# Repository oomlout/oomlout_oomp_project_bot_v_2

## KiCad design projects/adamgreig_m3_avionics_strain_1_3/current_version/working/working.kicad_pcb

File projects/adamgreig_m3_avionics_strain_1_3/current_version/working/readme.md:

# m3_avionics
 
## summary 
* id: adamgreig_m3_avionics_strain_1_3
* user: adamgreig
* name: m3_avionics
* board: strain_1_3
* repo: https://github.com/adamgreig/m3-avionics
* src_file_repo_kicad_pcb: m3dl/strain_1-3/strain_1-3.kicad_pcb
* src_file_repo_kicad_pcb_link: https://github.com/adamgreig/m3-avionics/tree/master/m3dl/strain_1-3/strain_1-3.kicad_pcb

* src_file_repo_sch: m3dl/strain_1-3/strain_1-3.sch
* src_file_repo_sch_link: https://github.com/adamgreig/m3-avionics/tree/master/m3dl/strain_1-3/strain_1-3.sch
* full details link: https://github.com/oomlout/oomlout_oomp_project_bot_v_2/tree/main/projects/adamgreig_m3_avionics_strain_1_3/current_version/working  

## schematic  
  
[schematic (pdf)](working_schematic.pdf) 

## pcb  

[board (pdf)](working.pdf)  

## working_bom
| Id | Designator | Footprint | Quantity | Designation | Supplier and ref |  | None | 
| --- | --- | --- | --- | --- | --- | --- | --- | 
| 1 | C1,C3,C4,C6,C15,C17 | 0603-L | 6 | 1n |  |  | [''] | 
| 2 | C2,C5,C16 | 0603-L | 3 | 10n |  |  | [''] | 
| 3 | C7,C8,C11,C12,C18,C20 | 0603-L | 6 | 8.2n |  |  | [''] | 
| 4 | C9,C10,C13,C14,C19,C21 | 0603-L | 6 | 82n |  |  | [''] | 
| 5 | IC1,IC3,IC6 | MSOP-8 | 3 | AD8226 |  |  | [''] | 
| 6 | IC2,IC4,IC7 | SC-70-5 | 3 | AD8541 |  |  | [''] | 
| 7 | IC5,IC8,IC9 | MSOP-8 | 3 | AD8656 |  |  | [''] | 
| 8 | J1 | TFML-110-02-L-D | 1 | WEST TOP |  |  | [''] | 
| 9 | J2 | TFML-110-02-L-D | 1 | EAST TOP |  |  | [''] | 
| 10 | J5 | TFML-110-02-L-D | 1 | SOUTH TOP |  |  | [''] | 
| 11 | R1,R2,R3,R4,R19,R20 | 0603-L | 6 | 3.74K |  |  | [''] | 
| 12 | R5,R6,R7,R8,R21,R22 | 0603-L | 6 | 10K |  |  | [''] | 
| 13 | R11,R12,R24 | 0603-L | 3 | 1.69K |  |  | [''] | 
| 14 | R13,R14,R25 | 0603-L | 3 | 6.04K |  |  | [''] | 
| 15 | R15,R16,R26 | 0603-L | 3 | 562R |  |  | [''] | 
| 16 | R17,R18,R27 | 0603-L | 3 | 17.8K |  |  | [''] | 
| 17 | J7 | Connector_Molex_PicoBlade_53048-0410 | 1 | S1 |  |  | [''] | 
| 18 | J8 | Connector_Molex_PicoBlade_53048-0410 | 1 | S3 |  |  | [''] | 
| 19 | J9 | Connector_Molex_PicoBlade_53048-0410 | 1 | S2 |  |  | [''] | 
| 20 | C35,C37 | 0402-L | 2 | 1u |  |  | [''] | 
| 21 | R32 | 0402-L | 1 | 110k |  |  | [''] | 
| 22 | IC10 | DFN-6-EP-ONSEMI | 1 | NCP380 |  |  | [''] | 
| 23 | J3 | SFML-110-02-L-D-LC | 1 | WEST BOT |  |  | [''] | 
| 24 | J4 | SFML-110-02-L-D-LC | 1 | EAST BOT |  |  | [''] | 
| 25 | J6 | SFML-110-02-L-D-LC | 1 | SOUTH BOT |  |  | [''] | 
| 26 | R9,R10,R23 | 0603-L | 3 | 330 |  |  | [''] | 
| 27 | C22,C23,C24,C25,C26,C27,C28,C29,C30,C31,C32,C33 | 0603-L | 12 | 100n |  |  | [''] | 
| 28 | C34 | 0603-L | 1 | 10u |  |  | [''] | 
| 29 | R28,R29,R30 | 0603 | 3 | 0R |  |  | [''] | 
| 30 | D1,D2,D3,D4,D5,D6,D7,D8,D9 | 0402 | 9 | ESD_DIODE |  |  | [''] | 

## bom_schematic
| Ref | Qnty | Value | Cmp name | Footprint | Description | Vendor | DNP | 
| --- | --- | --- | --- | --- | --- | --- | --- | 
| C1, C3, C4, C6, C15, C17 | 6 | 1n | C_Small | Capacitors_SMD:C_0603 |  |  |  | 
| C2, C5, C16 | 3 | 10n | C_Small | Capacitors_SMD:C_0603 |  |  |  | 
| C7, C8, C11, C12, C18, C20 | 6 | 8.2n | C_Small | Capacitors_SMD:C_0603 |  |  |  | 
| C9, C10, C13, C14, C19, C21 | 6 | 82n | C_Small | Capacitors_SMD:C_0603 |  |  |  | 
| C22, C23, C24, C25, C26, C27, C28, C29, C30, C31, C32, C33 | 12 | 100n | C_Small | agg:0603-L |  |  |  | 
| C34 | 1 | 10u | C_Small | agg:0603-L |  |  |  | 
| C35, C37 | 2 | 1u | C_Small | agg:0402-L |  |  |  | 
| D1, D2, D3, D4, D5, D6, D7, D8, D9 | 9 | ESD_DIODE | ESD_DIODE | agg:0402 |  |  |  | 
| IC1, IC3, IC6 | 3 | AD8226 | AD8226 | agg:MSOP-8 |  |  |  | 
| IC2, IC4, IC7 | 3 | AD8541 | AD8541 | agg:SC-70-5 |  |  |  | 
| IC5, IC8, IC9 | 3 | AD8656 | AD8656 | agg:MSOP-8 |  |  |  | 
| IC10 | 1 | NCP380 | NCP380 | agg:DFN-6-EP-ONSEMI |  |  |  | 
| J1 | 1 | WEST TOP | CONN_02x10 | agg:TFML-110-02-L-D |  |  |  | 
| J2 | 1 | EAST TOP | CONN_02x10 | agg:TFML-110-02-L-D |  |  |  | 
| J3 | 1 | WEST BOT | CONN_02x10 | agg:SFML-110-02-L-D-LC |  |  |  | 
| J4 | 1 | EAST BOT | CONN_02x10 | agg:SFML-110-02-L-D-LC |  |  |  | 
| J5 | 1 | SOUTH TOP | CONN_02x10 | agg:TFML-110-02-L-D |  |  |  | 
| J6 | 1 | SOUTH BOT | CONN_02x10 | agg:SFML-110-02-L-D-LC |  |  |  | 
| J7 | 1 | S1 | CONN_01x04 | Connectors_Molex:Connector_Molex_PicoBlade_53048-0410 |  |  |  | 
| J8 | 1 | S3 | CONN_01x04 | Connectors_Molex:Connector_Molex_PicoBlade_53048-0410 |  |  |  | 
| J9 | 1 | S2 | CONN_01x04 | Connectors_Molex:Connector_Molex_PicoBlade_53048-0410 |  |  |  | 
| R1, R2, R3, R4, R19, R20 | 6 | 3.74K | R | Resistors_SMD:R_0603 |  |  |  | 
| R5, R6, R7, R8, R21, R22 | 6 | 10K | R | Resistors_SMD:R_0603 |  |  |  | 
| R9, R10, R23 | 3 | 330 | R | Resistors_SMD:R_0603 |  |  |  | 
| R11, R12, R24 | 3 | 1.69K | R | Resistors_SMD:R_0603 |  |  |  | 
| R13, R14, R25 | 3 | 6.04K | R | Resistors_SMD:R_0603 |  |  |  | 
| R15, R16, R26 | 3 | 562R | R | Resistors_SMD:R_0603 |  |  |  | 
| R17, R18, R27 | 3 | 17.8K | R | Resistors_SMD:R_0603 |  |  |  | 
| R28, R29, R30 | 3 | 0R | R | agg:0603 |  |  |  | 
| R32 | 1 | 110k | R | agg:0402-L |  |  |  |

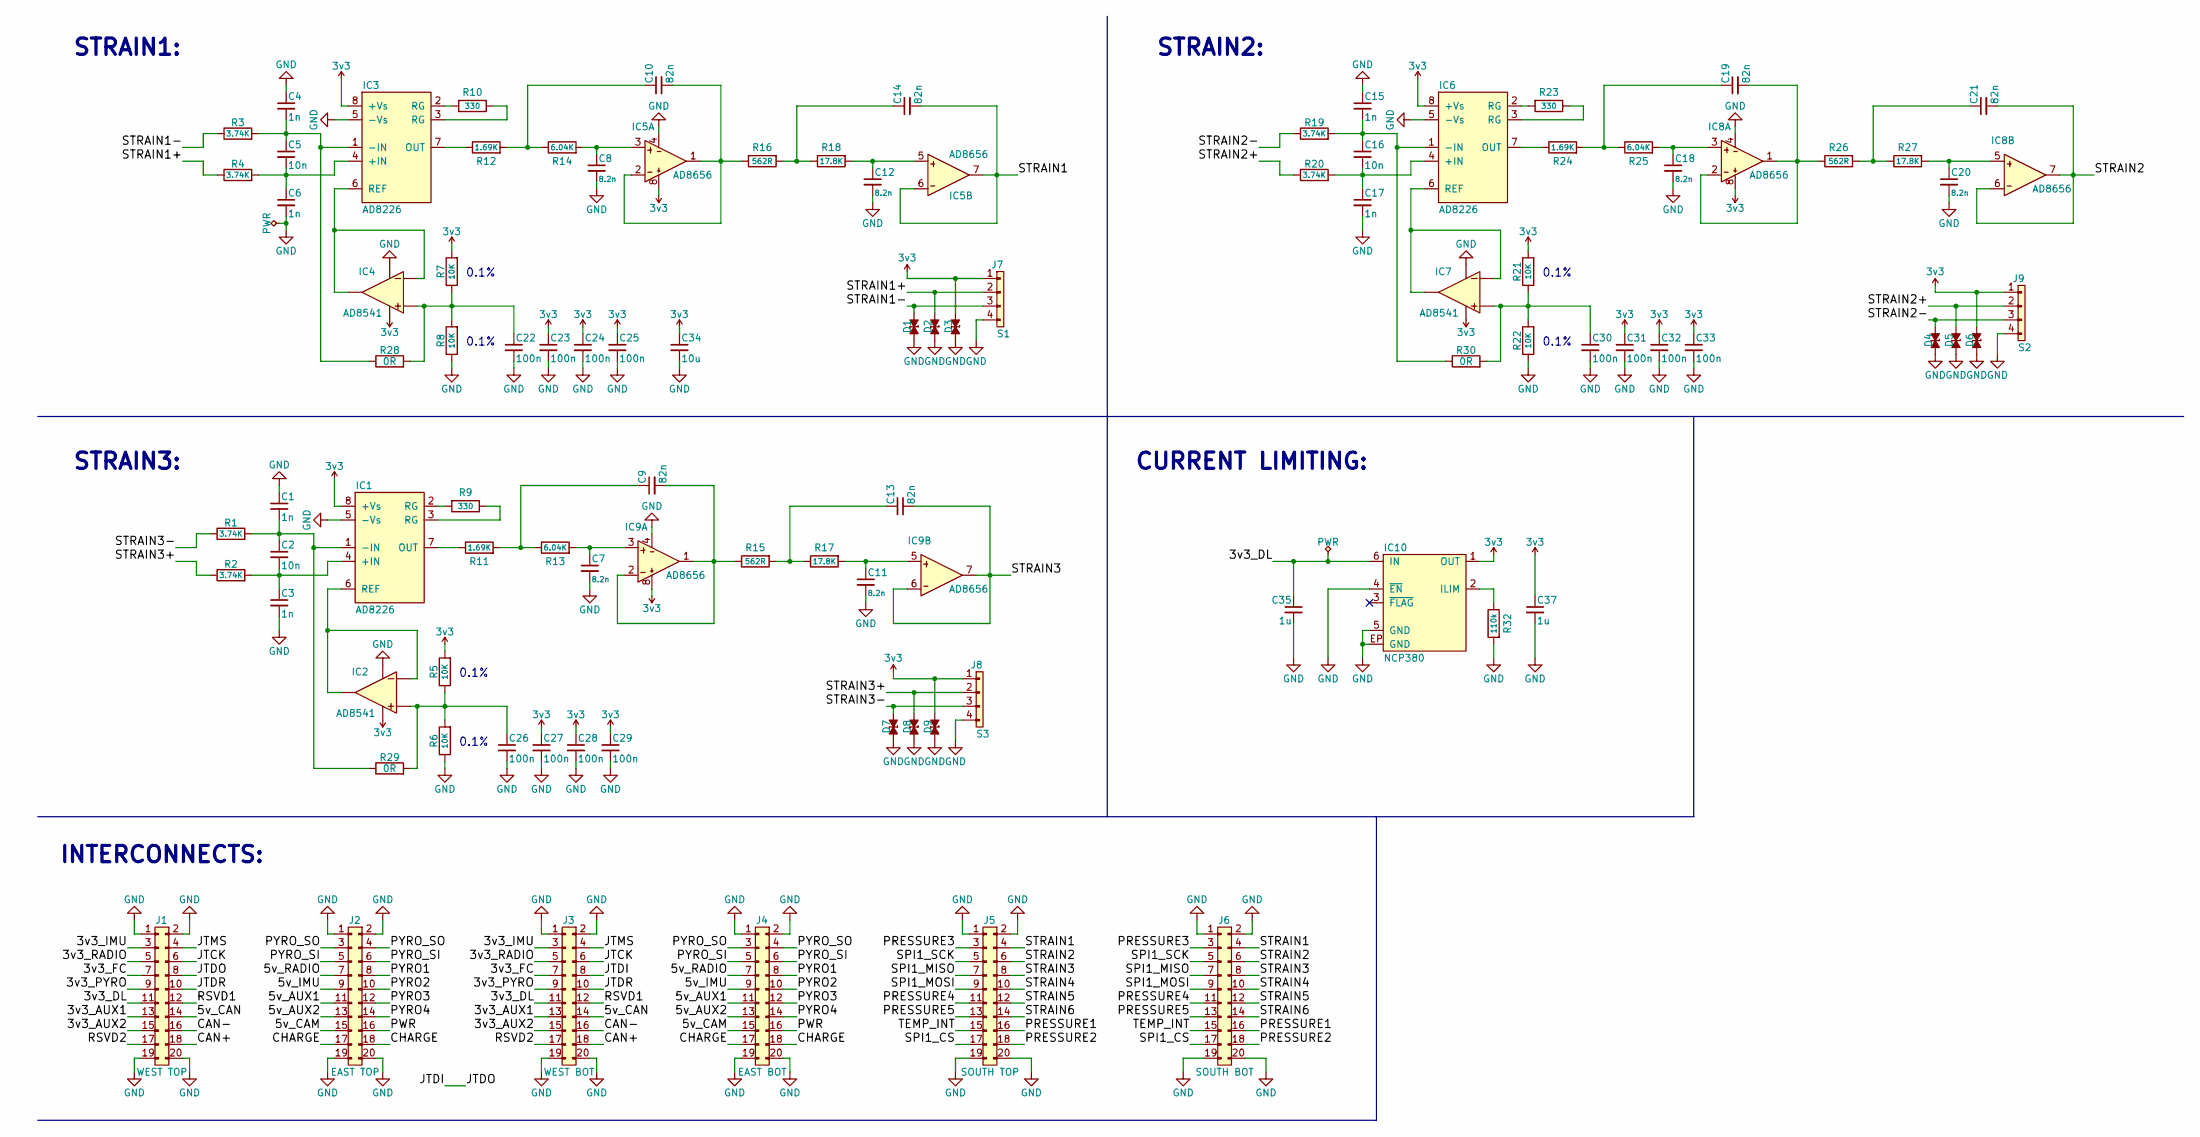
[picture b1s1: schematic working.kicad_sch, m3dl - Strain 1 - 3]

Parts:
C1, C3, C4, C6, C15, C17: 1n; C_0603; Farnell 1813443
C2, C5, C16: 10n; C_0603; Farnell 1457729
C7, C8, C11, C12, C18, C20: 8.2n; C_0603; Farnell 1865464
C9, C10, C13, C14, C19, C21: 82n; C_0603; Farnell 1865539
C22, C23, C24, C25, C26, C27, C28, C29, C30, C31, C32, C33: 100n; 0603-L; Farnell 2496834
C34: 10u; 0603-L; Farnell 2211164
C35, C37: 1u; 0402-L; Farnell 2346884
D1, D2, D3, D4, D5, D6, D7, D8, D9: ESD_DIODE; 0402; Farnell 2368169
IC1, IC3, IC6: AD8226; MSOP-8; Farnell 2462026
IC2, IC4, IC7: AD8541; SC-70-5; Farnell 1333254
IC5, IC8, IC9: AD8656; MSOP-8; Farnell 1858055
IC10: NCP380; DFN-6-EP-ONSEMI; Farnell 2464412
J1: WEST TOP; TFML-110-02-L-D
J2: EAST TOP; TFML-110-02-L-D
J3: WEST BOT; SFML-110-02-L-D-LC
J4: EAST BOT; SFML-110-02-L-D-LC
J5: SOUTH TOP; TFML-110-02-L-D
J6: SOUTH BOT; SFML-110-02-L-D-LC
J7: S1; Connector_Molex_PicoBlade_53048-0410
J8: S3; Connector_Molex_PicoBlade_53048-0410
J9: S2; Connector_Molex_PicoBlade_53048-0410
R1, R2, R3, R4, R19, R20: 3.74K; R_0603; Farnell 2059366
R5, R6, R7, R8, R21, R22: 10K; R_0603; Farnell 1697388
R9, R10, R23: 330; R_0603; Farnell 2502447
R11, R12, R24: 1.69K; R_0603; Farnell 2059339
R13, R14, R25: 6.04K; R_0603; Farnell 2059386
R15, R16, R26: 562R; R_0603; Farnell 1170763
R17, R18, R27: 17.8K; R_0603; Farnell 1170912
R28, R29, R30: 0R; 0603; Farnell 9331662
R32: 110k; 0402-L; Farnell 2502502

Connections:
3v3: C23.1, C24.1, C25.1, C27.1, C28.1, C29.1, C31.1, C32.1, C33.1, C34.1, C37.1, D3.2, D6.2, D9.2, IC1.8 (+Vs), IC2.5 (V+), IC3.8 (+Vs), IC4.5 (V+), IC5.8 (V+), IC6.8 (+Vs), IC7.5 (V+), IC8.8 (V+), IC9.8 (V+), IC10.1 (OUT), J7.1, J8.1, J9.1, R5.2, R7.2, R21.2
/3v3_AUX1: J1.13, J3.13
/3v3_AUX2: J1.15, J3.15
/3v3_DL: C35.1, IC10.6 (IN), J1.11, J3.11
/3v3_FC: J1.7, J3.7
/3v3_IMU: J1.3, J3.3
/3v3_PYRO: J1.9, J3.9
/3v3_RADIO: J1.5, J3.5
/5v_AUX1: J2.11, J4.11
/5v_AUX2: J2.13, J4.13
/5v_CAM: J2.15, J4.15
/5v_CAN: J1.14, J3.14
/5v_IMU: J2.9, J4.9
/5v_RADIO: J2.7, J4.7
/CAN+: J1.18, J3.18
/CAN-: J1.16, J3.16
/CHARGE: J2.17, J2.18, J4.17, J4.18
/JTCK: J1.6, J3.6
/JTDI: J1.8, J3.8
/JTDR: J1.10, J3.10
/JTMS: J1.4, J3.4
/PRESSURE1: J5.16, J6.16
/PRESSURE2: J5.18, J6.18
/PRESSURE3: J5.3, J6.3
/PRESSURE4: J5.11, J6.11
/PRESSURE5: J5.13, J6.13
/PWR: J2.16, J4.16
/PYRO1: J2.8, J4.8
/PYRO2: J2.10, J4.10
/PYRO3: J2.12, J4.12
/PYRO4: J2.14, J4.14
/PYRO_SI: J2.5, J2.6, J4.5, J4.6
/PYRO_SO: J2.3, J2.4, J4.3, J4.4
/RSVD1: J1.12, J3.12
/RSVD2: J1.17, J3.17
/SPI1_CS: J5.17, J6.17
/SPI1_MISO: J5.7, J6.7
/SPI1_MOSI: J5.9, J6.9
/SPI1_SCK: J5.5, J6.5
/STRAIN1: C14.2, IC5.6 (-IN), IC5.7 (OUT), J5.4, J6.4
/STRAIN1+: D2.2, J7.2, R4.1
/STRAIN1-: D1.2, J7.3, R3.1
/STRAIN2: C21.2, IC8.6 (-IN), IC8.7 (OUT), J5.6, J6.6
/STRAIN2+: D5.2, J9.2, R20.1
/STRAIN2-: D4.2, J9.3, R19.1
/STRAIN3: C13.2, IC9.6 (-IN), IC9.7 (OUT), J5.8, J6.8
/STRAIN3+: D8.2, J8.2, R2.1
/STRAIN3-: D7.2, J8.3, R1.1
/STRAIN4: J5.10, J6.10
/STRAIN5: J5.12, J6.12
/STRAIN6: J5.14, J6.14
/TEMP_INT: J5.15, J6.15
GND: C1.1, C3.2, C4.1, C6.2, C7.2, C8.2, C11.2, C12.2, C15.1, C17.2, C18.2, C20.2, C22.2, C23.2, C24.2, C25.2, C26.2, C27.2, C28.2, C29.2, C30.2, C31.2, C32.2, C33.2, C34.2, C35.2, C37.2, D1.1, D2.1, D3.1, D4.1, D5.1, D6.1, D7.1, D8.1, D9.1, IC1.5 (-Vs), IC2.2 (V-), IC3.5 (-Vs), IC4.2 (V-), IC5.4 (V-), IC6.5 (-Vs), IC7.2 (V-), IC8.4 (V-), IC9.4 (V-), IC10.4 (~EN), IC10.5 (GND), IC10.EP (GND), J1.1, J1.2, J1.19, J1.20, J2.1, J2.2, J2.19, J2.20, J3.1, J3.2, J3.19, J3.20, J4.1, J4.2, J4.19, J4.20, J5.1, J5.2, J5.19, J5.20, J6.1, J6.2, J6.19, J6.20, J7.4, J8.4, J9.4, R6.1, R8.1, R22.1, R32.2
unnamed: C1.2, C2.1, IC1.1 (-IN), R1.2, R29.1
unnamed: C2.2, C3.1, IC1.4 (+IN), R2.2
unnamed: C4.2, C5.1, IC3.1 (-IN), R3.2, R28.1
unnamed: C5.2, C6.1, IC3.4 (+IN), R4.2
unnamed: C7.1, IC9.3 (+IN), R13.2
unnamed: C8.1, IC5.3 (+IN), R14.2
unnamed: C9.1, R11.2, R13.1
unnamed: C9.2, IC9.1 (OUT), IC9.2 (-IN), R15.1
unnamed: C10.1, R12.2, R14.1
unnamed: C10.2, IC5.1 (OUT), IC5.2 (-IN), R16.1
unnamed: C11.1, IC9.5 (+IN), R17.2
unnamed: C12.1, IC5.5 (+IN), R18.2
unnamed: C13.1, R15.2, R17.1
unnamed: C14.1, R16.2, R18.1
unnamed: C15.2, C16.1, IC6.1 (-IN), R19.2, R30.1
unnamed: C16.2, C17.1, IC6.4 (+IN), R20.2
unnamed: C18.1, IC8.3 (+IN), R25.2
unnamed: C19.1, R24.2, R25.1
unnamed: C19.2, IC8.1 (OUT), IC8.2 (-IN), R26.1
unnamed: C20.1, IC8.5 (+IN), R27.2
unnamed: C21.1, R26.2, R27.1
unnamed: C22.1, IC4.3 (+), R7.1, R8.2, R28.2
unnamed: C26.1, IC2.3 (+), R5.1, R6.2, R29.2
unnamed: C30.1, IC7.3 (+), R21.1, R22.2, R30.2
unnamed: IC1.2 (RG), R9.2
unnamed: IC1.3 (RG), R9.1
unnamed: IC1.6 (REF), IC2.1 (OUT), IC2.4 (-)
unnamed: IC1.7 (OUT), R11.1
unnamed: IC3.2 (RG), R10.2
unnamed: IC3.3 (RG), R10.1
unnamed: IC3.6 (REF), IC4.1 (OUT), IC4.4 (-)
unnamed: IC3.7 (OUT), R12.1
unnamed: IC6.2 (RG), R23.2
unnamed: IC6.3 (RG), R23.1
unnamed: IC6.6 (REF), IC7.1 (OUT), IC7.4 (-)
unnamed: IC6.7 (OUT), R24.1
unnamed: IC10.2 (ILIM), R32.1

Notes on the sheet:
0.1%
INTERCONNECTS:
CURRENT LIMITING:
STRAIN3:
STRAIN2:
STRAIN1:

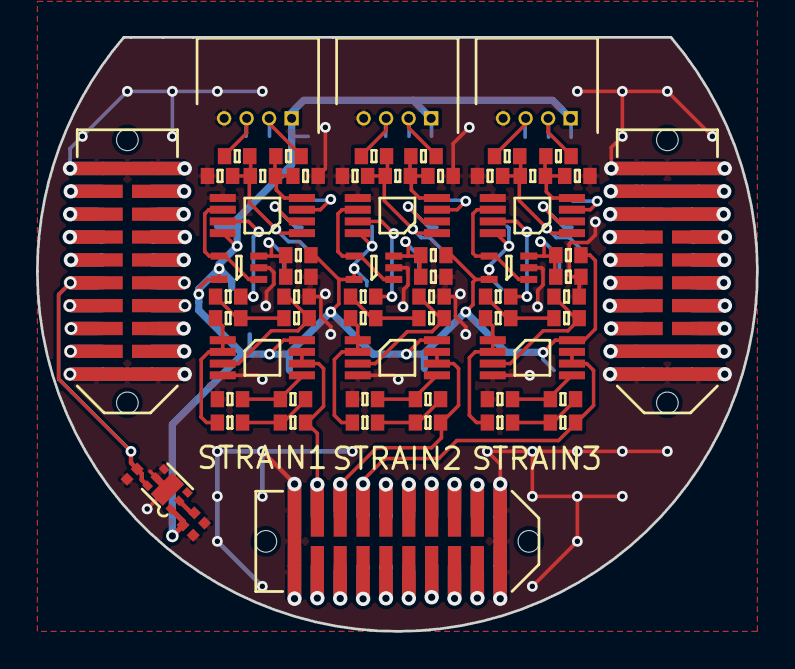
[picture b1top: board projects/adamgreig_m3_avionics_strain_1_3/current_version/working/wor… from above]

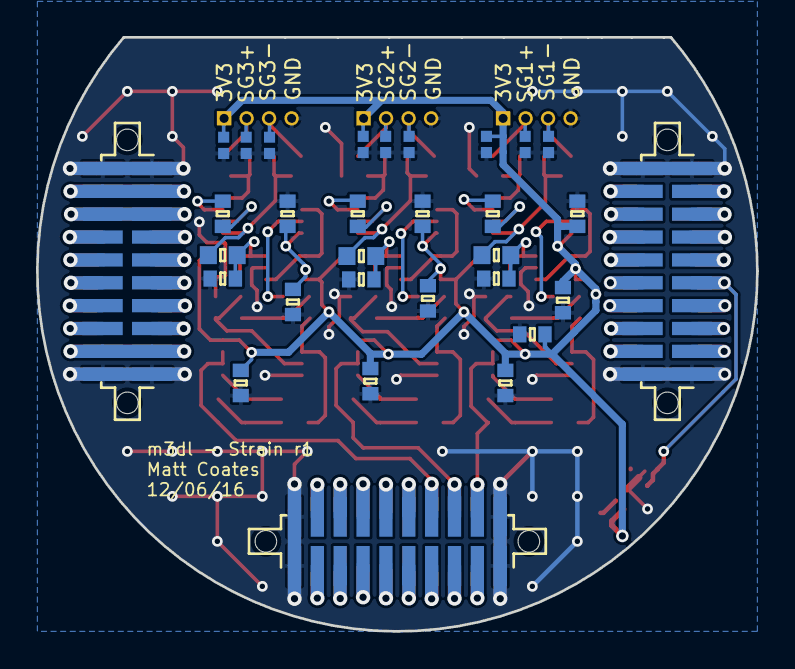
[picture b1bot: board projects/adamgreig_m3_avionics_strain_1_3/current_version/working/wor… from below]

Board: 2 copper layers, 40.0 x 33.0 mm, 95 parts (31 on the bottom side), 90 nets.

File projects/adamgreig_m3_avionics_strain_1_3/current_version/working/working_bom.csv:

"Id";"Designator";"Footprint";"Quantity";"Designation";"Supplier and ref";
1;"C1,C3,C4,C6,C15,C17";"0603-L";6;"1n";;;
2;"C2,C5,C16";"0603-L";3;"10n";;;
3;"C7,C8,C11,C12,C18,C20";"0603-L";6;"8.2n";;;
4;"C9,C10,C13,C14,C19,C21";"0603-L";6;"82n";;;
5;"IC1,IC3,IC6";"MSOP-8";3;"AD8226";;;
6;"IC2,IC4,IC7";"SC-70-5";3;"AD8541";;;
7;"IC5,IC8,IC9";"MSOP-8";3;"AD8656";;;
8;"J1";"TFML-110-02-L-D";1;"WEST TOP";;;
9;"J2";"TFML-110-02-L-D";1;"EAST TOP";;;
10;"J5";"TFML-110-02-L-D";1;"SOUTH TOP";;;
11;"R1,R2,R3,R4,R19,R20";"0603-L";6;"3.74K";;;
12;"R5,R6,R7,R8,R21,R22";"0603-L";6;"10K";;;
13;"R11,R12,R24";"0603-L";3;"1.69K";;;
14;"R13,R14,R25";"0603-L";3;"6.04K";;;
15;"R15,R16,R26";"0603-L";3;"562R";;;
16;"R17,R18,R27";"0603-L";3;"17.8K";;;
17;"J7";"Connector_Molex_PicoBlade_53048-0410";1;"S1";;;
18;"J8";"Connector_Molex_PicoBlade_53048-0410";1;"S3";;;
19;"J9";"Connector_Molex_PicoBlade_53048-0410";1;"S2";;;
20;"C35,C37";"0402-L";2;"1u";;;
21;"R32";"0402-L";1;"110k";;;
22;"IC10";"DFN-6-EP-ONSEMI";1;"NCP380";;;
23;"J3";"SFML-110-02-L-D-LC";1;"WEST BOT";;;
24;"J4";"SFML-110-02-L-D-LC";1;"EAST BOT";;;
25;"J6";"SFML-110-02-L-D-LC";1;"SOUTH BOT";;;
26;"R9,R10,R23";"0603-L";3;"330";;;
27;"C22,C23,C24,C25,C26,C27,C28,C29,C30,C31,C32,C33";"0603-L";12;"100n";;;
28;"C34";"0603-L";1;"10u";;;
29;"R28,R29,R30";"0603";3;"0R";;;
30;"D1,D2,D3,D4,D5,D6,D7,D8,D9";"0402";9;"ESD_DIODE";;;

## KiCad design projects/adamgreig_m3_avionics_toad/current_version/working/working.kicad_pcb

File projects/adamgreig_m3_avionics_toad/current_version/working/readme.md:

# m3_avionics
 
## summary 
* id: adamgreig_m3_avionics_toad
* user: adamgreig
* name: m3_avionics
* board: toad
* repo: https://github.com/adamgreig/m3-avionics
* src_file_repo_kicad_pcb: TOAD/pcb/TOAD.kicad_pcb
* src_file_repo_kicad_pcb_link: https://github.com/adamgreig/m3-avionics/tree/master/TOAD/pcb/TOAD.kicad_pcb

* src_file_repo_sch: TOAD/pcb/TOAD.sch
* src_file_repo_sch_link: https://github.com/adamgreig/m3-avionics/tree/master/TOAD/pcb/TOAD.sch
* full details link: https://github.com/oomlout/oomlout_oomp_project_bot_v_2/tree/main/projects/adamgreig_m3_avionics_toad/current_version/working  

## schematic  
  
[schematic (pdf)](working_schematic.pdf) 

## pcb  

[board (pdf)](working.pdf)  

## working_bom
| Id | Designator | Footprint | Quantity | Designation | Supplier and ref |  | None | 
| --- | --- | --- | --- | --- | --- | --- | --- | 
| 1 | C1,C33 | 0603-L | 2 | 2.2uF |  |  | [''] | 
| 2 | C2,C34 | 0402 | 2 | 100nF |  |  | [''] | 
| 3 | C3,C35 | 0402 | 2 | 220pF |  |  | [''] | 
| 4 | C4,C7,C8,C9,C12,C13,C14,C60 | 0402 | 8 | 100n |  |  | [''] | 
| 5 | C5,C37 | 0603-L | 2 | 1uF |  |  | [''] | 
| 6 | C6,C38 | 0402 | 2 | 100pF |  |  | [''] | 
| 7 | C10,C11 | 0603-L | 2 | 2u2 |  |  | [''] | 
| 8 | C15 | 0603 | 1 | 4u7 |  |  | [''] | 
| 9 | C16,C26,C31,C42,C43,C47 | 0603-L | 6 | 1u |  |  | [''] | 
| 10 | C17,C48 | 0402 | 2 | 3pF |  |  | [''] | 
| 11 | C18,C49 | 0402 | 2 | 33pF |  |  | [''] | 
| 12 | C19,C50 | 0402 | 2 | 3.9pF |  |  | [''] | 
| 13 | C20,C51 | 0402 | 2 | 1pF |  |  | [''] | 
| 14 | C21,C32,C36,C44,C58 | 0603-L | 5 | 100n |  |  | [''] | 
| 15 | C22,C52 | 0402 | 2 | 5.1pF |  |  | [''] | 
| 16 | C23,C53 | 0402 | 2 | 2.7pF |  |  | [''] | 
| 17 | C28,C30,C57,C59 | 0402 | 4 | 4.7pF |  |  | [''] | 
| 18 | C29,C46 | 0603-L | 2 | 10n |  |  | [''] | 
| 19 | C39,C45 | 0603-L | 2 | 4u7 |  |  | [''] | 
| 20 | C40,C41 | 0603-L | 2 | 1n |  |  | [''] | 
| 21 | D1,D2,D3,D4,D5,D6,D7,D15,D17,D18 | 0402-L | 10 | ESD_DIODE |  |  | [''] | 
| 22 | D8,D9,D10,D11,D12,D13,D14,D16 | 0603-LED | 8 | LED |  |  | [''] | 
| 23 | IC1 | LQFP-64 | 1 | STM32F405RxTx |  |  | [''] | 
| 24 | IC2,IC9 | QFN-20-EP-SI | 2 | Si4463 |  |  | [''] | 
| 25 | IC3 | MAX-M8Q | 1 | MAX-M8Q |  |  | [''] | 
| 26 | IC4 | SC-70-6 | 1 | SN74LVC1G0832 |  |  | [''] | 
| 27 | IC5,IC12 | TSLP7-4 | 2 | BGS12AL7 |  |  | [''] | 
| 28 | IC6,IC10 | MSOP-8 | 2 | ADP3335 |  |  | [''] | 
| 29 | IC7 | QFN-16-EP-TI | 1 | BQ24232HA |  |  | [''] | 
| 30 | IC8 | SOT-23-5 | 1 | NC7SZ04 |  |  | [''] | 
| 31 | IC11 | MSOP-10 | 1 | CS2100-CP |  |  | [''] | 
| 32 | IC13 | DFN-10-SL18860DC | 1 | SL18860DC |  |  | [''] | 
| 33 | J1 | SIL-254P-05 | 1 | USB |  |  | [''] | 
| 34 | J2 | S03B-PASK-2 | 1 | BATT |  |  | [''] | 
| 35 | J3 | S03B-PASK-2 | 1 | SWITCH |  |  | [''] | 
| 36 | L2,L9 | 0402 | 2 | 20nH |  |  | [''] | 
| 37 | L3,L10 | 0402 | 2 | 24nH |  |  | [''] | 
| 38 | L4,L11 | 0402 | 2 | 15nH |  |  | [''] | 
| 39 | L5,L6,L12,L13 | 0402 | 4 | 11nH |  |  | [''] | 
| 40 | L7,L14 | 0402 | 2 | 9.1nH |  |  | [''] | 
| 41 | P1,P3,P4 | SMA-EDGE | 3 | SMA |  |  | [''] | 
| 42 | P2 | TC2030-NL | 1 | SWD_TC |  |  | [''] | 
| 43 | R1,R2,R11,R12 | 0603-L | 4 | 10K |  |  | [''] | 
| 44 | R3,R6,R7,R8,R10 | 0603-L | 5 | 47K |  |  | [''] | 
| 45 | R4,R5 | 0603-L | 2 | 110k |  |  | [''] | 
| 46 | R9 | 0603-L | 1 | 4k32 |  |  | [''] | 
| 47 | R13 | 0603-L | 1 | 1M |  |  | [''] | 
| 48 | R14 | 0603-L | 1 | 1k |  |  | [''] | 
| 49 | R15,R16,R17,R18,R19,R20,R21,R22 | 0603-L | 8 | 120R |  |  | [''] | 
| 50 | U1 | MICROSD_MOLEX_503398-1892 | 1 | MICROSD |  |  | [''] | 
| 51 | X8,X9,X12,X13 | M3_MOUNT | 4 | Mount |  |  | [''] | 
| 52 | X10,X14 | BMI-S-201-F | 2 | RF Frame |  |  | [''] | 
| 53 | Y1 | XTAL-25x20 | 1 | 26M TCXO |  |  | [''] | 
| 54 | L1,L8 | 0402 | 2 | 120nH |  |  | [''] | 
| 55 | G*** | toad | 1 | LOGO |  |  | [''] | 
| 56 | TP1,TP2,TP3,TP4,TP5,TP6,TP7,TP8,TP9,TP10,TP11,TP12 | TESTPAD | 12 | TESTPAD |  |  | [''] | 
| 57 | R23,R24,R25,R26 | 0402 | 4 | 10K |  |  | [''] | 

## bom_schematic
| Ref | Qnty | Value | Cmp name | Footprint | Description | Vendor | DNP | 
| --- | --- | --- | --- | --- | --- | --- | --- | 
| C1, C33 | 2 | 2.2uF | C_Small | agg:0603-L |  |  |  | 
| C2, C34 | 2 | 100nF | C_Small | agg:0402 |  |  |  | 
| C3, C35 | 2 | 220pF | C_Small | agg:0402 |  |  |  | 
| C4, C7, C8, C9, C12, C13, C14, C60 | 8 | 100n | C_Small | agg:0402 |  |  |  | 
| C5, C37 | 2 | 1uF | C_Small | agg:0603-L |  |  |  | 
| C6, C38 | 2 | 100pF | C_Small | agg:0402 |  |  |  | 
| C10, C11 | 2 | 2u2 | C_Small | agg:0603-L |  |  |  | 
| C15 | 1 | 4u7 | C_Small | agg:0603 |  |  |  | 
| C16, C26, C31, C42, C43, C47 | 6 | 1u | C_Small | agg:0603-L |  |  |  | 
| C17, C48 | 2 | 3pF | C_Small | agg:0402 |  |  |  | 
| C18, C49 | 2 | 33pF | C_Small | agg:0402 |  |  |  | 
| C19, C50 | 2 | 3.9pF | C_Small | agg:0402 |  |  |  | 
| C20, C51 | 2 | 1pF | C_Small | agg:0402 |  |  |  | 
| C21, C32, C36, C44, C58 | 5 | 100n | C_Small | agg:0603-L |  |  |  | 
| C22, C52 | 2 | 5.1pF | C_Small | agg:0402 |  |  |  | 
| C23, C53 | 2 | 2.7pF | C_Small | agg:0402 |  |  |  | 
| C28, C30, C57, C59 | 4 | 4.7pF | C_Small | agg:0402 |  |  |  | 
| C29, C46 | 2 | 10n | C_Small | agg:0603-L |  |  |  | 
| C39, C45 | 2 | 4u7 | C_Small | agg:0603-L |  |  |  | 
| C40, C41 | 2 | 1n | C_Small | agg:0603-L |  |  |  | 
| D1, D2, D3, D4, D5, D6, D7, D15, D17, D18 | 10 | ESD_DIODE | ESD_DIODE | agg:0402-L |  |  |  | 
| D8, D9, D10, D11, D12, D13, D14, D16 | 8 | LED | LED-RESCUE-TOAD | agg:0603-LED |  |  |  | 
| IC1 | 1 | STM32F405RxTx | STM32F405RxTx | agg:LQFP-64 |  |  |  | 
| IC2, IC9 | 2 | Si4463 | Si4460 | agg:QFN-20-EP-SI |  |  |  | 
| IC3 | 1 | MAX-M8Q | MAX-M8Q | agg:MAX-M8Q |  |  |  | 
| IC4 | 1 | SN74LVC1G0832 | SN74LVC1G0832 | agg:SC-70-6 |  |  |  | 
| IC5, IC12 | 2 | BGS12AL7 | BGS12AL7 | agg:TSLP7-4 |  |  |  | 
| IC6, IC10 | 2 | ADP3335 | ADP3335 | agg:MSOP-8 |  |  |  | 
| IC7 | 1 | BQ24232HA | BQ24232HA | agg:QFN-16-EP-TI |  |  |  | 
| IC8 | 1 | NC7SZ04 | NC7SZ04 | agg:SOT-23-5 |  |  |  | 
| IC11 | 1 | CS2100-CP | CS2100-CP | agg:MSOP-10 |  |  |  | 
| IC13 | 1 | SL18860DC | SL18860DC | agg:DFN-10-SL18860DC |  |  |  | 
| J1 | 1 | USB | CONN_01x05 | agg:SIL-254P-05 |  |  |  | 
| J2 | 1 | BATT | CONN_01x03 | agg:S03B-PASK-2 |  |  |  | 
| J3 | 1 | SWITCH | CONN_01x03 | agg:S03B-PASK-2 |  |  |  | 
| L1, L8 | 2 | 120nH | L_Small | agg:0402 |  |  |  | 
| L2, L9 | 2 | 20nH | L_Small | agg:0402 |  |  |  | 
| L3, L10 | 2 | 24nH | L_Small | agg:0402 |  |  |  | 
| L4, L11 | 2 | 15nH | L_Small | agg:0402 |  |  |  | 
| L5, L6, L12, L13 | 4 | 11nH | L_Small | agg:0402 |  |  |  | 
| L7, L14 | 2 | 9.1nH | L_Small | agg:0402 |  |  |  | 
| P1, P3, P4 | 3 | SMA | COAX | agg:SMA-EDGE |  |  |  | 
| P2 | 1 | SWD_TC | SWD_TC | agg:TC2030-NL |  |  |  | 
| R1, R2, R11, R12 | 4 | 10K | R-RESCUE-TOAD | agg:0603-L |  |  |  | 
| R3, R6, R7, R8, R10 | 5 | 47K | R-RESCUE-TOAD | agg:0603-L |  |  |  | 
| R4, R5 | 2 | 110k | R-RESCUE-TOAD | agg:0603-L |  |  |  | 
| R9 | 1 | 4k32 | R-RESCUE-TOAD | agg:0603-L |  |  |  | 
| R13 | 1 | 1M | R-RESCUE-TOAD | agg:0603-L |  |  |  | 
| R14 | 1 | 1k | R-RESCUE-TOAD | agg:0603-L |  |  |  | 
| R15, R16, R17, R18, R19, R20, R21, R22 | 8 | 120R | R-RESCUE-TOAD | agg:0603-L |  |  |  | 
| R23, R24, R25, R26 | 4 | 10K | R-RESCUE-TOAD | agg:0402 |  |  |  | 
| TP1, TP2, TP3, TP4, TP5, TP6, TP7, TP8, TP9, TP10, TP11, TP12 | 12 | TESTPAD | TESTPAD | agg:TESTPAD |  |  |  | 
| U1 | 1 | MICROSD | MICROSD | agg:MICROSD_MOLEX_503398-1892 |  |  |  | 
| X1 | 1 | USB Cap | PART |  |  |  |  | 
| X2 | 1 | USB Mini-B | PART |  |  |  |  | 
| X3 | 1 | Case | PART |  |  |  |  | 
| X4, X5 | 2 | SMA Panel | PART |  |  |  |  | 
| X6 | 1 | PWR Switch | PART |  |  |  |  | 
| X7 | 1 | Battery | PART |  |  |  |  | 
| X8, X9, X12, X13 | 4 | Mount | PART | agg:M3_MOUNT |  |  |  | 
| X10, X14 | 2 | RF Frame | PART | Library:BMI-S-201-F |  |  |  | 
| X11, X15 | 2 | RF Cover | PART |  |  |  |  | 
| Y1 | 1 | 26M TCXO | TCXO | agg:XTAL-25x20 |  |  |  |

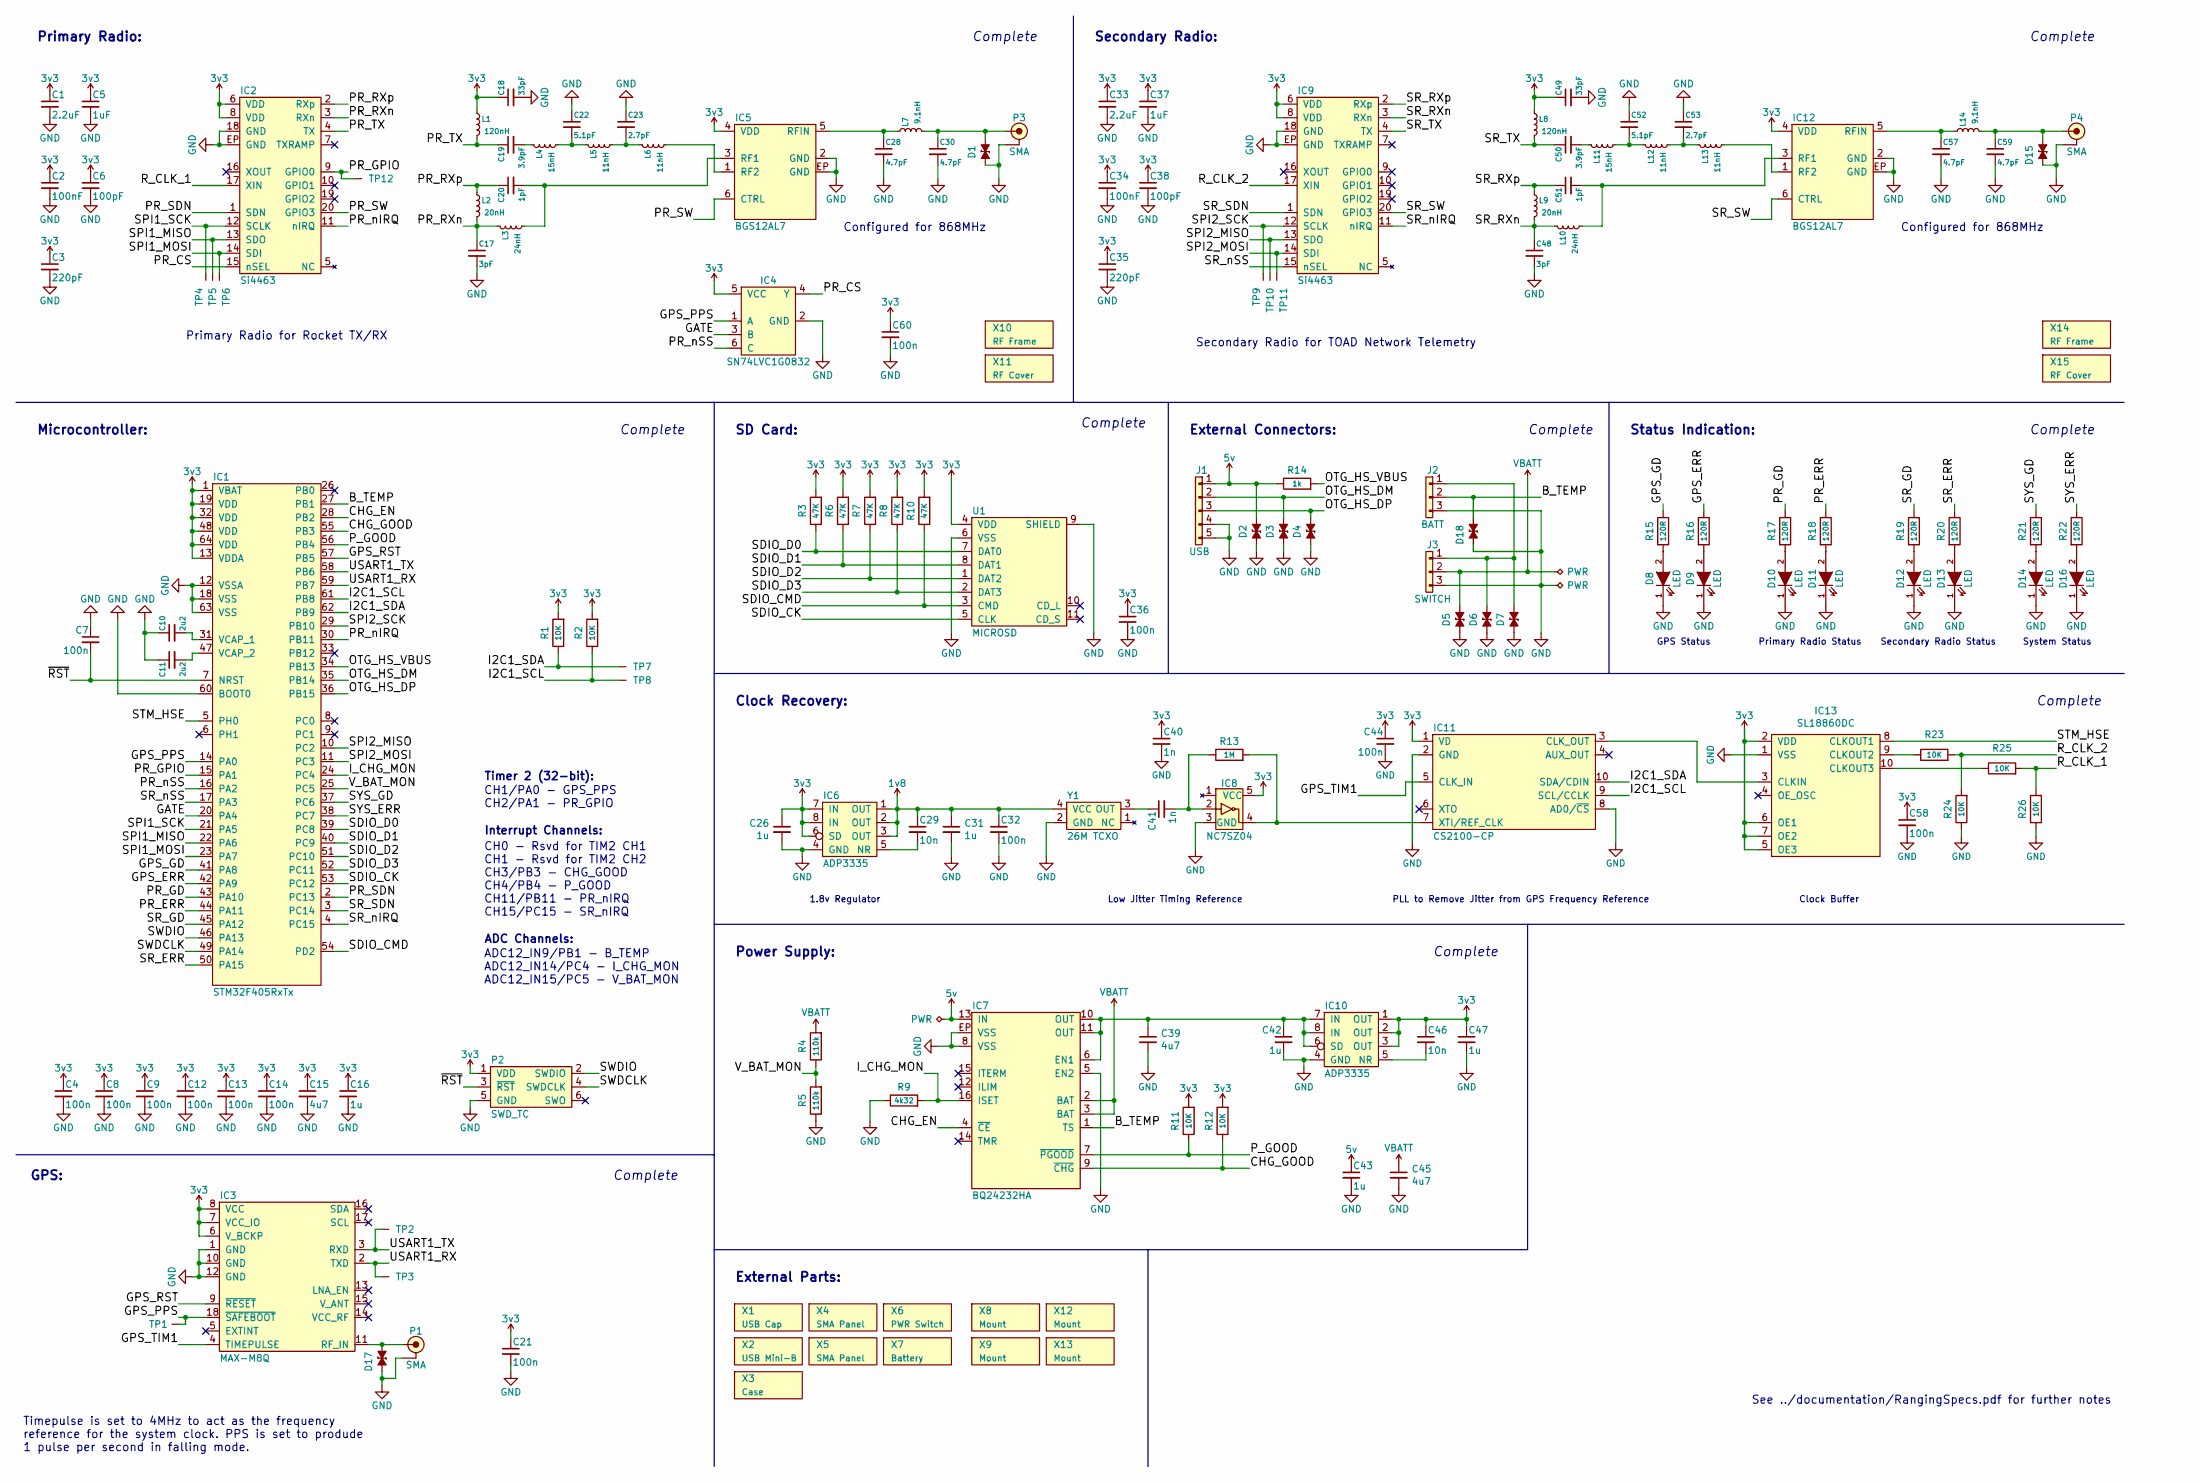
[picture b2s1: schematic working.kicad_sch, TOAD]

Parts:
C1, C33: 2.2uF; 0603-L; Farnell 2346896
C2, C34: 100nF; 0402; Farnell 1828860
C3, C35: 220pF; 0402; Farnell 2496800
C4, C7, C8, C9, C12, C13, C14, C60: 100n; 0402; Farnell 9402047
C5, C37: 1uF; 0603-L; Farnell 2112849
C6, C38: 100pF; 0402; Farnell 2496792
C10, C11: 2u2; 0603-L; Farnell 1797012
C15: 4u7; 0603; Farnell 2496930
C16, C26, C31, C42, C43, C47: 1u; 0603-L; Farnell 1865556
C17, C48: 3pF; 0402; Farnell 2524984
C18, C49: 33pF; 0402; Farnell 2434643
C19, C50: 3.9pF; 0402; Farnell 2672775
C20, C51: 1pF; 0402; Farnell 2133992
C21, C32, C36, C44, C58: 100n; 0603-L; Farnell 2496834
C22, C52: 5.1pF; 0402; Farnell 2688498
C23, C53: 2.7pF; 0402; Farnell 2672771
C28, C30, C57, C59: 4.7pF; 0402; Farnell 2332509
C29, C46: 10n; 0603-L; Farnell 2496825
C39, C45: 4u7; 0603-L; Farnell 2496930
C40, C41: 1n; 0603-L; Farnell 2496882
D1, D2, D3, D4, D5, D6, D7, D15, D17, D18: ESD_DIODE; 0402-L; Farnell 2368169
D8, D10, D12, D14: LED; 0603-LED; Farnell 2290328
D9, D11, D13, D16: LED; 0603-LED; Farnell 2290329
IC1: STM32F405RxTx; LQFP-64; Farnell 2064363
IC2, IC9: Si4463; QFN-20-EP-SI; Farnell 2462637
IC3: MAX-M8Q
IC4: SN74LVC1G0832; SC-70-6; Farnell 2406965
IC5, IC12: BGS12AL7; TSLP7-4; Farnell 2480594
IC6: ADP3335; MSOP-8; Farnell 2376932
IC7: BQ24232HA; QFN-16-EP-TI; Farnell 2576286
IC8: NC7SZ04; SOT-23-5; Farnell 1417667
IC10: ADP3335; MSOP-8; Farnell 2067775
IC11: CS2100-CP; MSOP-10; Mouser 777-CS2100CP-CZZ
IC13: SL18860DC; DFN-10-SL18860DC; Mouser 634-SL18860DC
J1: USB; SIL-254P-05
J2: BATT; S03B-PASK-2; Farnell 1830748
J3: SWITCH; S03B-PASK-2; Farnell 1830748
L1, L8: 120nH; 0402; Farnell 2285871
L2, L9: 20nH; 0402; Farnell 1748728
L3, L10: 24nH; 0402; Farnell 2470344
L4, L11: 15nH; 0402; Farnell 1762621
L5, L6, L12, L13: 11nH; 0402; Farnell 2116067
L7, L14: 9.1nH; 0402; Farnell 1762616
P1: SMA; SMA-EDGE
P2: SWD_TC; TC2030-NL
P3, P4: SMA; SMA-EDGE; Farnell 1608592
R1, R2, R11, R12: 10K; 0603-L; Farnell 9238603
R3, R6, R7, R8, R10: 47K; 0603-L; Farnell 9238689
R4, R5: 110k; 0603-L; Farnell 2502402
R9: 4k32; 0603-L; Farnell 2670808
R13: 1M; 0603-L; Farnell 1469746
R14: 1k; 0603-L; Farnell 2309108
R15, R16, R17, R18, R19, R20, R21, R22: 120R; 0603-L; Farnell 9238379
R23, R24, R25, R26: 10K; 0402; Farnell 2379805
TP1, TP2, TP3, TP4, TP5, TP6, TP7, TP8, TP9, TP10, TP11, TP12: TESTPAD
U1: MICROSD; MICROSD_MOLEX_503398-1892; Farnell 2358234
X1: USB Cap
X2: USB Mini-B
X3: Case
X4, X5: SMA Panel; Farnell 2096227
X6: PWR Switch
X7: Battery; Farnell 2401856
X8, X9, X12, X13: Mount; M3_MOUNT
X10, X14: RF Frame; BMI-S-201-F; Farnell 2497715
X11, X15: RF Cover; Farnell 2497714
Y1: 26M TCXO; XTAL-25x20; Farnell 2405785

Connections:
1v8: C29.1, C31.1, C32.1, IC6.1 (OUT), IC6.2 (OUT), IC6.3 (OUT), Y1.4 (VCC)
3v3: C1.1, C2.1, C3.1, C4.1, C5.1, C6.1, C8.1, C9.1, C12.1, C13.1, C14.1, C15.1, C16.1, C18.1, C21.1, C26.1, C33.1, C34.1, C35.1, C36.1, C37.1, C38.1, C40.1, C44.1, C46.1, C47.1, C49.1, C58.1, C60.1, IC1.1 (VBAT), IC1.13 (VDDA), IC1.19 (VDD), IC1.32 (VDD), IC1.48 (VDD), IC1.64 (VDD), IC2.6 (VDD), IC2.8 (VDD), IC3.6 (V_BCKP), IC3.7 (VCC_IO), IC3.8 (VCC), IC4.5 (VCC), IC5.4 (VDD), IC6.6 (SD), IC6.7 (IN), IC6.8 (IN), IC8.5 (VCC), IC9.6 (VDD), IC9.8 (VDD), IC10.1 (OUT), IC10.2 (OUT), IC10.3 (OUT), IC11.1 (VD), IC12.4 (VDD), IC13.2 (VDD), IC13.5 (OE3), IC13.6 (OE1), IC13.7 (OE2), L1.1, L8.1, P2.1 (VDD), R1.2, R2.2, R3.2, R6.2, R7.2, R8.2, R10.2, R11.2, R12.2, U1.4 (VDD)
5v: C43.1, D2.1, IC7.13 (IN), J1.1, R14.1
/B_TEMP: D18.1, IC1.27 (PB1), IC7.1 (TS), J2.2
/CHG_EN: IC1.28 (PB2), IC7.4 (~CE)
/CHG_GOOD: IC1.55 (PB3), IC7.9 (~CHG), R12.1
/GATE: IC1.20 (PA4), IC4.3 (B)
/GPS_ERR: IC1.42 (PA9), R16.1
/GPS_GD: IC1.41 (PA8), R15.1
/GPS_PPS: IC1.14 (PA0), IC3.18 (~SAFEBOOT), IC4.1 (A), TP1.1
/GPS_RST: IC1.57 (PB5), IC3.9 (~RESET)
/GPS_TIM1: IC3.4 (TIMEPULSE), IC11.5 (CLK_IN)
/I2C1_SCL: IC1.61 (PB8), IC11.9 (SCL/CCLK), R2.1, TP8.1
/I2C1_SDA: IC1.62 (PB9), IC11.10 (SDA/CDIN), R1.1, TP7.1
/I_CHG_MON: IC1.24 (PC4), IC7.16 (ISET), R9.2
/OTG_HS_DM: D3.1, IC1.35 (PB14), J1.2
/OTG_HS_DP: D4.1, IC1.36 (PB15), J1.3
/OTG_HS_VBUS: IC1.34 (PB13), R14.2
/PR_CS: IC2.15 (nSEL), IC4.4 (Y)
/PR_ERR: IC1.44 (PA11), R18.1
/PR_GD: IC1.43 (PA10), R17.1
/PR_GPIO: IC1.15 (PA1), IC2.9 (GPIO0), TP12.1
/PR_RXn: C17.1, IC2.3 (RXn), L2.2, L3.1
/PR_RXp: C20.1, IC2.2 (RXp), L2.1
/PR_SDN: IC1.2 (PC13), IC2.1 (SDN)
/PR_SW: IC2.20 (GPIO3), IC5.6 (CTRL)
/PR_TX: C19.1, IC2.4 (TX), L1.2
/PR_nIRQ: IC1.30 (PB11), IC2.11 (nIRQ)
/PR_nSS: IC1.16 (PA2), IC4.6 (C)
/P_GOOD: IC1.56 (PB4), IC7.7 (~PGOOD), R11.1
/R_CLK_1: IC2.17 (XIN), R25.2, R26.2
/R_CLK_2: IC9.17 (XIN), R23.2, R24.2
/SDIO_CK: IC1.53 (PC12), U1.5 (CLK)
/SDIO_CMD: IC1.54 (PD2), R10.1, U1.3 (CMD)
/SDIO_D0: IC1.39 (PC8), R3.1, U1.7 (DAT0)
/SDIO_D1: IC1.40 (PC9), R6.1, U1.8 (DAT1)
/SDIO_D2: IC1.51 (PC10), R7.1, U1.1 (DAT2)
/SDIO_D3: IC1.52 (PC11), R8.1, U1.2 (DAT3)
/SPI1_MISO: IC1.22 (PA6), IC2.13 (SDO), TP5.1
/SPI1_MOSI: IC1.23 (PA7), IC2.14 (SDI), TP6.1
/SPI1_SCK: IC1.21 (PA5), IC2.12 (SCLK), TP4.1
/SPI2_MISO: IC1.10 (PC2), IC9.13 (SDO), TP10.1
/SPI2_MOSI: IC1.11 (PC3), IC9.14 (SDI), TP11.1
/SPI2_SCK: IC1.29 (PB10), IC9.12 (SCLK), TP9.1
/SR_ERR: IC1.50 (PA15), R20.1
/SR_GD: IC1.45 (PA12), R19.1
/SR_RXn: C48.1, IC9.3 (RXn), L9.2, L10.1
/SR_RXp: C51.1, IC9.2 (RXp), L9.1
/SR_SDN: IC1.3 (PC14), IC9.1 (SDN)
/SR_SW: IC9.20 (GPIO3), IC12.6 (CTRL)
/SR_TX: C50.1, IC9.4 (TX), L8.2
/SR_nIRQ: IC1.4 (PC15), IC9.11 (nIRQ)
/SR_nSS: IC1.17 (PA3), IC9.15 (nSEL)
/STM_HSE: IC1.5 (PH0), IC13.8 (CLKOUT1)
/SWDCLK: IC1.49 (PA14), P2.4 (SWDCLK)
/SWDIO: IC1.46 (PA13), P2.2 (SWDIO)
/SYS_ERR: IC1.38 (PC7), R22.1
/SYS_GD: IC1.37 (PC6), R21.1
/USART1_RX: IC1.59 (PB7), IC3.2 (TXD), TP3.1
/USART1_TX: IC1.58 (PB6), IC3.3 (RXD), TP2.1
/V_BAT_MON: IC1.25 (PC5), R4.1, R5.2
/~RST: C7.2, IC1.7 (NRST), P2.3 (~RST)
GND: C1.2, C2.2, C3.2, C4.2, C5.2, C6.2, C7.1, C8.2, C9.2, C10.1, C11.1, C12.2, C13.2, C14.2, C15.2, C16.2, C17.2, C18.2, C21.2, C22.1, C23.1, C26.2, C28.2, C30.2, C31.2, C32.2, C33.2, C34.2, C35.2, C36.2, C37.2, C38.2, C39.2, C40.2, C42.2, C43.2, C44.2, C45.2, C47.2, C48.2, C49.2, C52.1, C53.1, C57.2, C58.2, C59.2, C60.2, D1.2, D2.2, D3.2, D4.2, D5.2, D6.2, D7.2, D8.1 (K), D9.1 (K), D10.1 (K), D11.1 (K), D12.1 (K), D13.1 (K), D14.1 (K), D15.2, D16.1 (K), D17.2, D18.2, IC1.12 (VSSA), IC1.18 (VSS), IC1.60 (BOOT0), IC1.63 (VSS), IC2.18 (GND), IC2.EP (GND), IC3.1 (GND), IC3.10 (GND), IC3.12 (GND), IC4.2 (GND), IC5.2 (GND), IC5.EP (GND), IC6.4 (GND), IC7.5 (EN2), IC7.8 (VSS)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
unnamed: C10.2, IC1.31 (VCAP_1)
unnamed: C11.2, IC1.47 (VCAP_2)
unnamed: C19.2, L4.1
unnamed: C20.2, IC5.3 (RF1), L3.2
unnamed: C22.2, L4.2, L5.1
unnamed: C23.2, L5.2, L6.1
unnamed: C28.1, IC5.5 (RFIN), L7.1
unnamed: C29.2, IC6.5 (NR)
unnamed: C30.1, D1.1, L7.2, P3.1 (RF)
unnamed: C39.1, C42.1, IC7.6 (EN1), IC7.10 (OUT), IC7.11 (OUT), IC10.6 (SD), IC10.7 (IN), IC10.8 (IN)
unnamed: C41.1, Y1.3 (OUT)
unnamed: C41.2, IC8.2, R13.1
unnamed: C46.2, IC10.5 (NR)
unnamed: C50.2, L11.1
unnamed: C51.2, IC12.3 (RF1), L10.2
unnamed: C52.2, L11.2, L12.1
unnamed: C53.2, L12.2, L13.1
unnamed: C57.1, IC12.5 (RFIN), L14.1
unnamed: C59.1, D15.1, L14.2, P4.1 (RF)
unnamed: D6.1, D7.1, J2.1, J3.1
unnamed: D8.2 (A), R15.2
unnamed: D9.2 (A), R16.2
unnamed: D10.2 (A), R17.2
unnamed: D11.2 (A), R18.2
unnamed: D12.2 (A), R19.2
unnamed: D13.2 (A), R20.2
unnamed: D14.2 (A), R21.2
unnamed: D16.2 (A), R22.2
unnamed: D17.1, IC3.11 (RF_IN), P1.1 (RF)
unnamed: IC5.1 (RF2), L6.2
unnamed: IC11.3 (CLK_OUT), IC13.3 (CLKIN)
unnamed: IC8.4, IC11.7 (XTI/REF_CLK), R13.2
unnamed: IC12.1 (RF2), L13.2
unnamed: IC13.9 (CLKOUT2), R23.1
unnamed: IC13.10 (CLKOUT3), R25.1
VBATT: C45.1, D5.1, IC7.2 (BAT), IC7.3 (BAT), J3.2, R4.2

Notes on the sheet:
CH1/PA0 - GPS_PPS CH2/PA1 - PR_GPIO
1.8v Regulator
Complete
See ../documentation/RangingSpecs.pdf for further notes
Microcontroller:
PLL to Remove Jitter from GPS Frequency Reference
ADC12_IN9/PB1 - B_TEMP ADC12_IN14/PC4 - I_CHG_MON ADC12_IN15/PC5 - V_BAT_MON
Power Supply:
Timepulse is set to 4MHz to act as the frequency reference for the system clock. PPS is set to produde 1 pulse per second in falling mode.
External Parts:
Clock Buffer
GPS Status
Secondary Radio:
Primary Radio:
Primary Radio for Rocket TX/RX
Timer 2 (32-bit):
External Connectors:
Status Indication:
Low Jitter Timing Reference
Interrupt Channels:
ADC Channels:
GPS:
Secondary Radio Status
Configured for 868MHz
SD Card:
Clock Recovery:
Primary Radio Status
CH0 - Rsvd for TIM2 CH1 CH1 - Rsvd for TIM2 CH2 CH3/PB3 - CHG_GOOD CH4/PB4 - P_GOOD CH11/PB11 - PR_nIRQ CH15/PC15 - SR_nIRQ
System Status
Secondary Radio for TOAD Network Telemetry

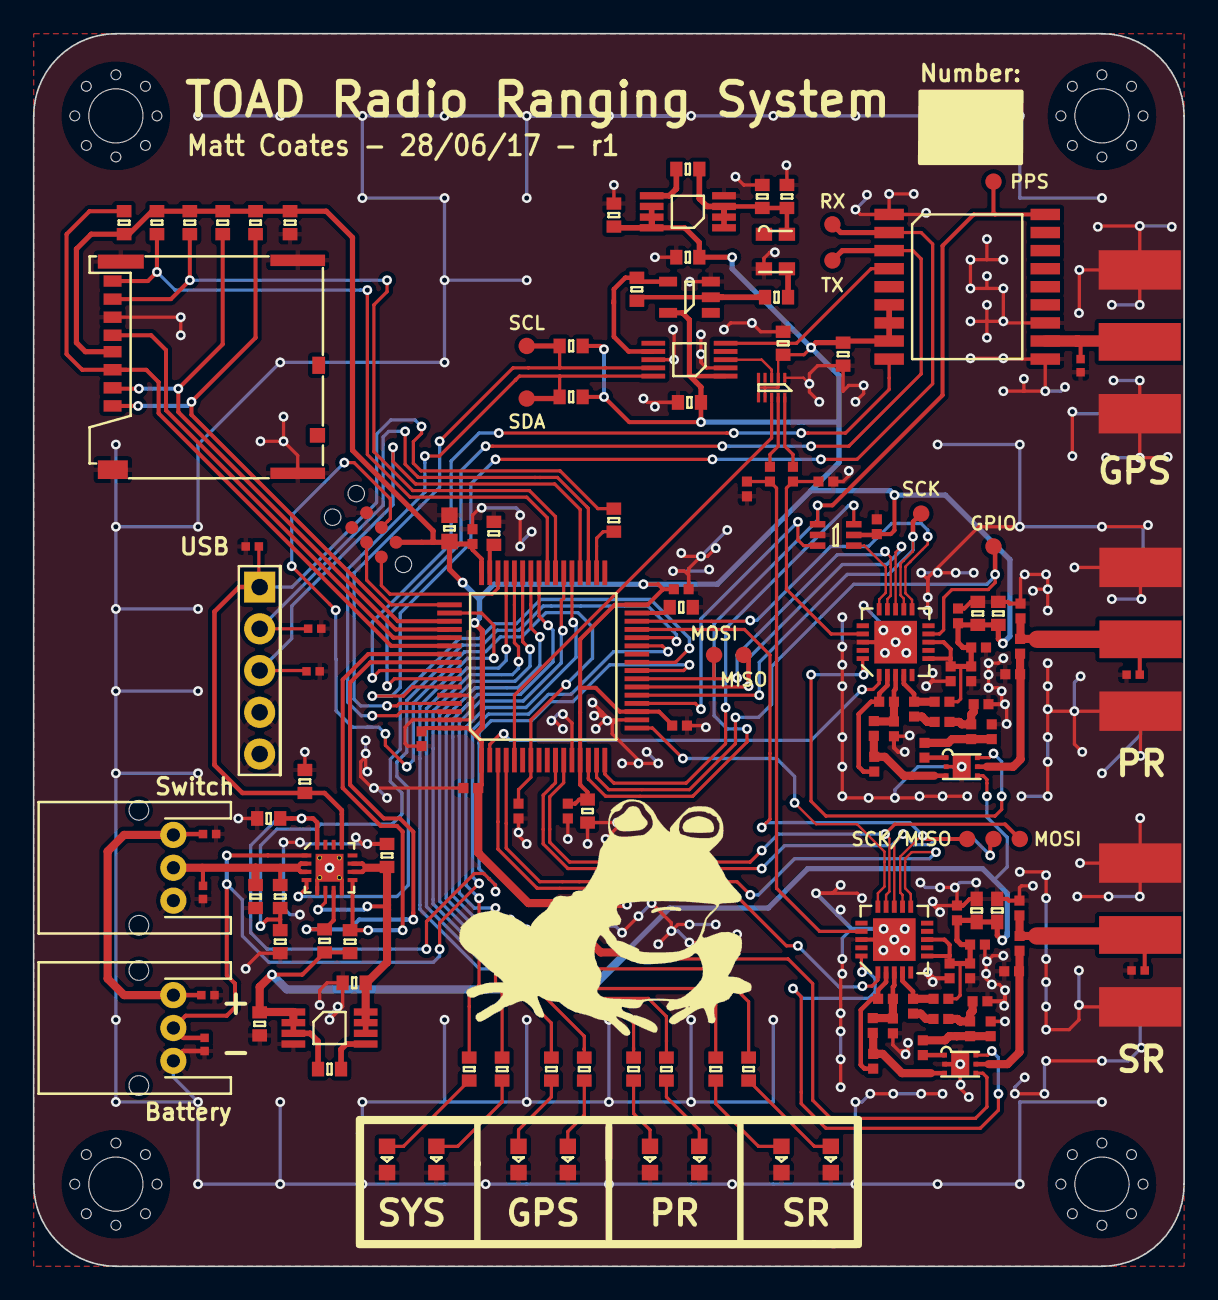
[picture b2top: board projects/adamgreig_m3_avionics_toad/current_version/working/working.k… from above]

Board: 2 copper layers, 70.0 x 75.0 mm, 152 parts (0 on the bottom side), 99 nets.

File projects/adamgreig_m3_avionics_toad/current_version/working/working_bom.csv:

"Id";"Designator";"Footprint";"Quantity";"Designation";"Supplier and ref";
1;"C1,C33";"0603-L";2;"2.2uF";;;
2;"C2,C34";"0402";2;"100nF";;;
3;"C3,C35";"0402";2;"220pF";;;
4;"C4,C7,C8,C9,C12,C13,C14,C60";"0402";8;"100n";;;
5;"C5,C37";"0603-L";2;"1uF";;;
6;"C6,C38";"0402";2;"100pF";;;
7;"C10,C11";"0603-L";2;"2u2";;;
8;"C15";"0603";1;"4u7";;;
9;"C16,C26,C31,C42,C43,C47";"0603-L";6;"1u";;;
10;"C17,C48";"0402";2;"3pF";;;
11;"C18,C49";"0402";2;"33pF";;;
12;"C19,C50";"0402";2;"3.9pF";;;
13;"C20,C51";"0402";2;"1pF";;;
14;"C21,C32,C36,C44,C58";"0603-L";5;"100n";;;
15;"C22,C52";"0402";2;"5.1pF";;;
16;"C23,C53";"0402";2;"2.7pF";;;
17;"C28,C30,C57,C59";"0402";4;"4.7pF";;;
18;"C29,C46";"0603-L";2;"10n";;;
19;"C39,C45";"0603-L";2;"4u7";;;
20;"C40,C41";"0603-L";2;"1n";;;
21;"D1,D2,D3,D4,D5,D6,D7,D15,D17,D18";"0402-L";10;"ESD_DIODE";;;
22;"D8,D9,D10,D11,D12,D13,D14,D16";"0603-LED";8;"LED";;;
23;"IC1";"LQFP-64";1;"STM32F405RxTx";;;
24;"IC2,IC9";"QFN-20-EP-SI";2;"Si4463";;;
25;"IC3";"MAX-M8Q";1;"MAX-M8Q";;;
26;"IC4";"SC-70-6";1;"SN74LVC1G0832";;;
27;"IC5,IC12";"TSLP7-4";2;"BGS12AL7";;;
28;"IC6,IC10";"MSOP-8";2;"ADP3335";;;
29;"IC7";"QFN-16-EP-TI";1;"BQ24232HA";;;
30;"IC8";"SOT-23-5";1;"NC7SZ04";;;
31;"IC11";"MSOP-10";1;"CS2100-CP";;;
32;"IC13";"DFN-10-SL18860DC";1;"SL18860DC";;;
33;"J1";"SIL-254P-05";1;"USB";;;
34;"J2";"S03B-PASK-2";1;"BATT";;;
35;"J3";"S03B-PASK-2";1;"SWITCH";;;
36;"L2,L9";"0402";2;"20nH";;;
37;"L3,L10";"0402";2;"24nH";;;
38;"L4,L11";"0402";2;"15nH";;;
39;"L5,L6,L12,L13";"0402";4;"11nH";;;
40;"L7,L14";"0402";2;"9.1nH";;;
41;"P1,P3,P4";"SMA-EDGE";3;"SMA";;;
42;"P2";"TC2030-NL";1;"SWD_TC";;;
43;"R1,R2,R11,R12";"0603-L";4;"10K";;;
44;"R3,R6,R7,R8,R10";"0603-L";5;"47K";;;
45;"R4,R5";"0603-L";2;"110k";;;
46;"R9";"0603-L";1;"4k32";;;
47;"R13";"0603-L";1;"1M";;;
48;"R14";"0603-L";1;"1k";;;
49;"R15,R16,R17,R18,R19,R20,R21,R22";"0603-L";8;"120R";;;
50;"U1";"MICROSD_MOLEX_503398-1892";1;"MICROSD";;;
51;"X8,X9,X12,X13";"M3_MOUNT";4;"Mount";;;
52;"X10,X14";"BMI-S-201-F";2;"RF Frame";;;
53;"Y1";"XTAL-25x20";1;"26M TCXO";;;
54;"L1,L8";"0402";2;"120nH";;;
55;"G***";"toad";1;"LOGO";;;
56;"TP1,TP2,TP3,TP4,TP5,TP6,TP7,TP8,TP9,TP10,TP11,TP12";"TESTPAD";12;"TESTPAD";;;
57;"R23,R24,R25,R26";"0402";4;"10K";;;
